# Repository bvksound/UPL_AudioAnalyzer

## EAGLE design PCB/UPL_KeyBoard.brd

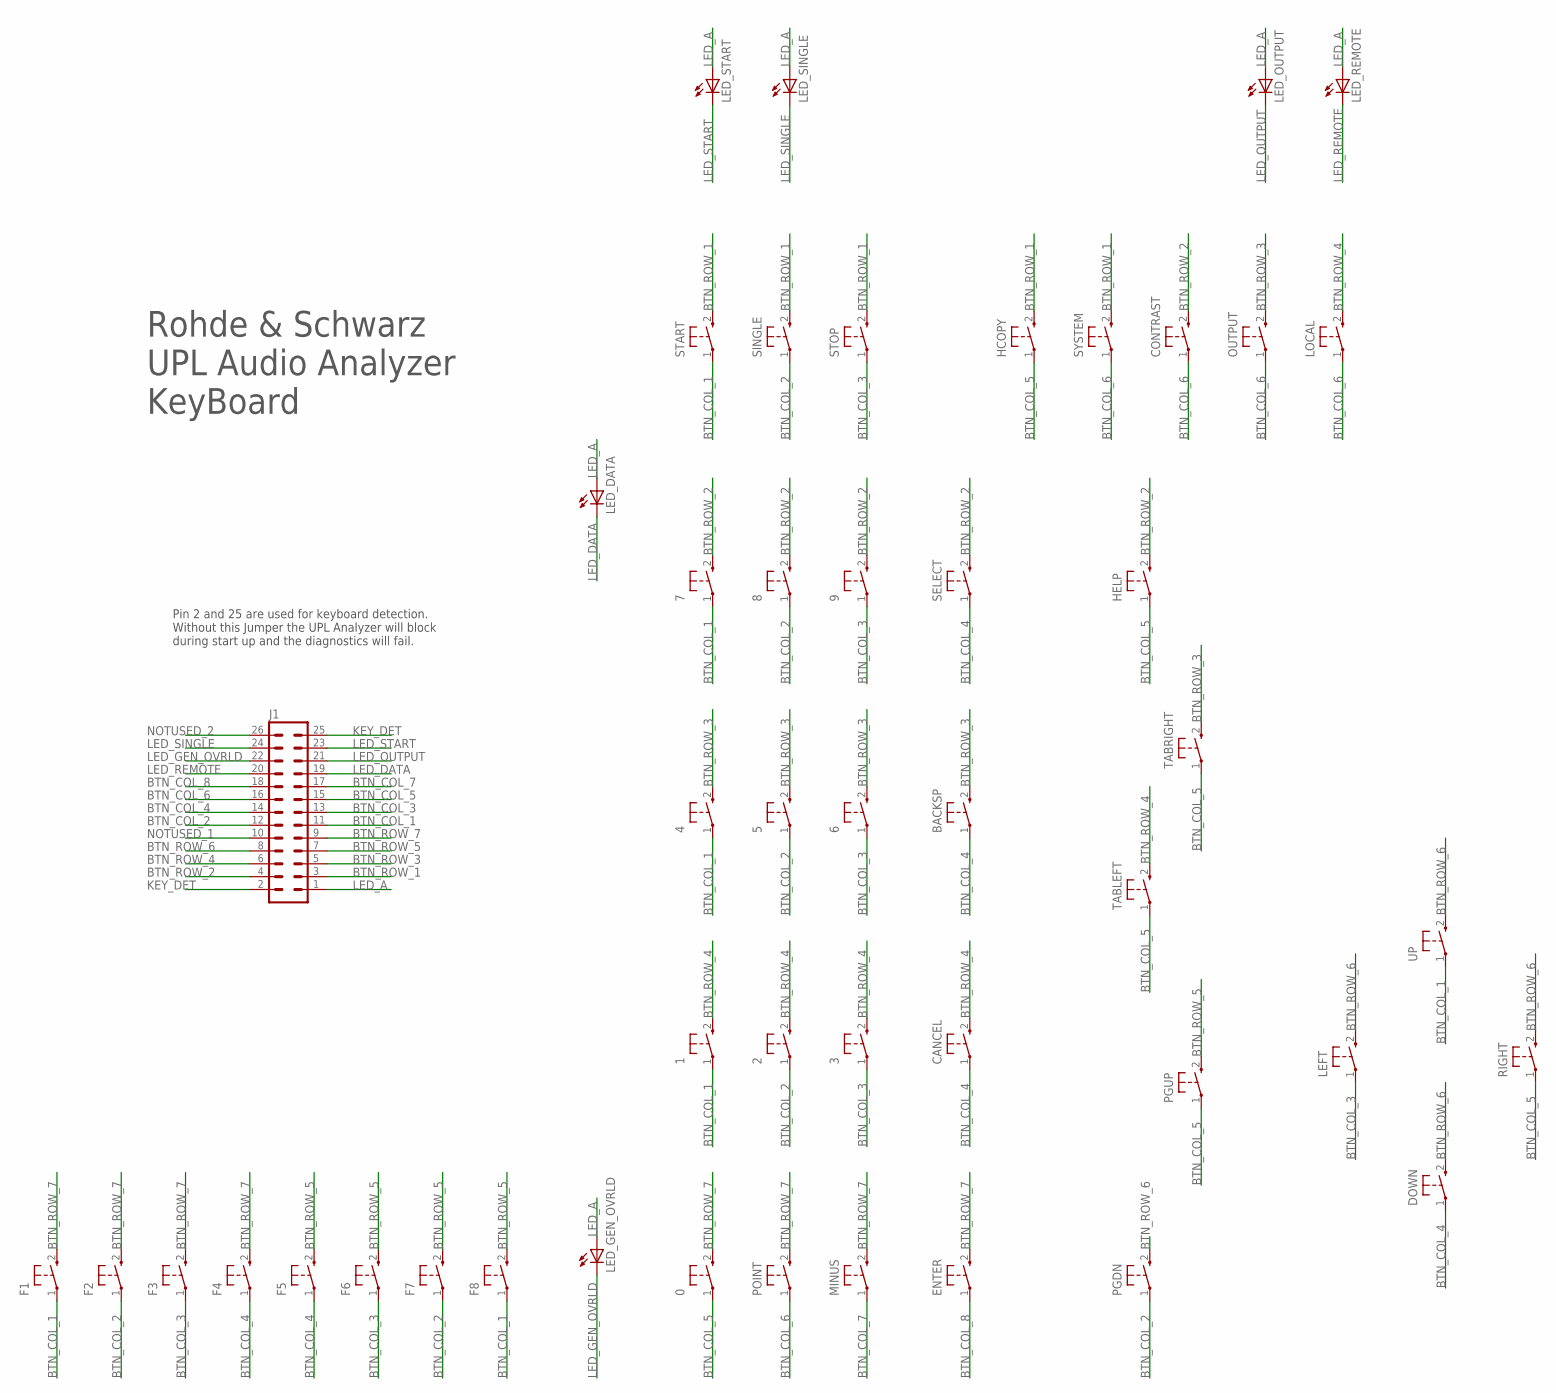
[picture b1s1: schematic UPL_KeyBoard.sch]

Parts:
0, 1, 2, 3, 4, 5, 6, 7, 8, 9: ALPS_SKQYAFE010
BACKSP: ALPS_SKQYAFE010
CANCEL: ALPS_SKQYAFE010
CONTRAST: ALPS_SKQYAFE010
DOWN: ALPS_SKQYAFE010
ENTER: ALPS_SKQYAFE010
F1, F2, F3, F4, F5, F6, F7, F8: ALPS_SKQYAFE010
HCOPY: ALPS_SKQYAFE010
HELP: ALPS_SKQYAFE010
J1: ML26
LED_DATA: LEDCHIPLED_1206; CHIPLED_1206
LED_GEN_OVRLD: LEDCHIPLED_1206; CHIPLED_1206
LED_OUTPUT: LEDCHIPLED_1206; CHIPLED_1206
LED_REMOTE: LEDCHIPLED_1206; CHIPLED_1206
LED_SINGLE: LEDCHIPLED_1206; CHIPLED_1206
LED_START: LEDCHIPLED_1206; CHIPLED_1206
LEFT: ALPS_SKQYAFE010
LOCAL: ALPS_SKQYAFE010
MINUS: ALPS_SKQYAFE010
OUTPUT: ALPS_SKQYAFE010
PGDN: ALPS_SKQYAFE010
PGUP: ALPS_SKQYAFE010
POINT: ALPS_SKQYAFE010
RIGHT: ALPS_SKQYAFE010
SELECT: ALPS_SKQYAFE010
SINGLE: ALPS_SKQYAFE010
START: ALPS_SKQYAFE010
STOP: ALPS_SKQYAFE010
SYSTEM: ALPS_SKQYAFE010
TABLEFT: ALPS_SKQYAFE010
TABRIGHT: ALPS_SKQYAFE010
UP: ALPS_SKQYAFE010

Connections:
BTN_COL_1: 1.1, 4.1, 7.1, F1.1, F8.1, J1.11, START.1, UP.1
BTN_COL_2: 2.1, 5.1, 8.1, F2.1, F7.1, J1.12, PGDN.1, SINGLE.1
BTN_COL_3: 3.1, 6.1, 9.1, F3.1, F6.1, J1.13, LEFT.1, STOP.1
BTN_COL_4: BACKSP.1, CANCEL.1, DOWN.1, F4.1, F5.1, J1.14, SELECT.1
BTN_COL_5: 0.1, HCOPY.1, HELP.1, J1.15, PGUP.1, RIGHT.1, TABLEFT.1, TABRIGHT.1
BTN_COL_6: CONTRAST.1, J1.16, LOCAL.1, OUTPUT.1, POINT.1, SYSTEM.1
BTN_COL_7: J1.17, MINUS.1
BTN_COL_8: ENTER.1, J1.18
BTN_ROW_1: HCOPY.2 (3), J1.3, SINGLE.2 (3), START.2 (3), STOP.2 (3), SYSTEM.2 (3)
BTN_ROW_2: 7.2 (3), 8.2 (3), 9.2 (3), CONTRAST.2 (3), HELP.2 (3), J1.4, SELECT.2 (3)
BTN_ROW_3: 4.2 (3), 5.2 (3), 6.2 (3), BACKSP.2 (3), J1.5, OUTPUT.2 (3), TABRIGHT.2 (3)
BTN_ROW_4: 1.2 (3), 2.2 (3), 3.2 (3), CANCEL.2 (3), J1.6, LOCAL.2 (3), TABLEFT.2 (3)
BTN_ROW_5: F5.2 (3), F6.2 (3), F7.2 (3), F8.2 (3), J1.7, PGUP.2 (3)
BTN_ROW_6: DOWN.2 (3), J1.8, LEFT.2 (3), PGDN.2 (3), RIGHT.2 (3), UP.2 (3)
BTN_ROW_7: 0.2 (3), ENTER.2 (3), F1.2 (3), F2.2 (3), F3.2 (3), F4.2 (3), J1.9, MINUS.2 (3), POINT.2 (3)
KEY_DET: J1.2, J1.25
LED_A: J1.1, LED_DATA.A, LED_GEN_OVRLD.A, LED_OUTPUT.A, LED_REMOTE.A, LED_SINGLE.A, LED_START.A
LED_DATA: J1.19, LED_DATA.C
LED_GEN_OVRLD: J1.22, LED_GEN_OVRLD.C
LED_OUTPUT: J1.21, LED_OUTPUT.C
LED_REMOTE: J1.20, LED_REMOTE.C
LED_SINGLE: J1.24, LED_SINGLE.C
LED_START: J1.23, LED_START.C
NOTUSED_1: J1.10
NOTUSED_2: J1.26

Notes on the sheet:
Pin 2 and 25 are used for keyboard detection. Without this Jumper the UPL Analyzer will block during start up and the diagnostics will fail.
Rohde & Schwarz UPL Audio Analyzer KeyBoard

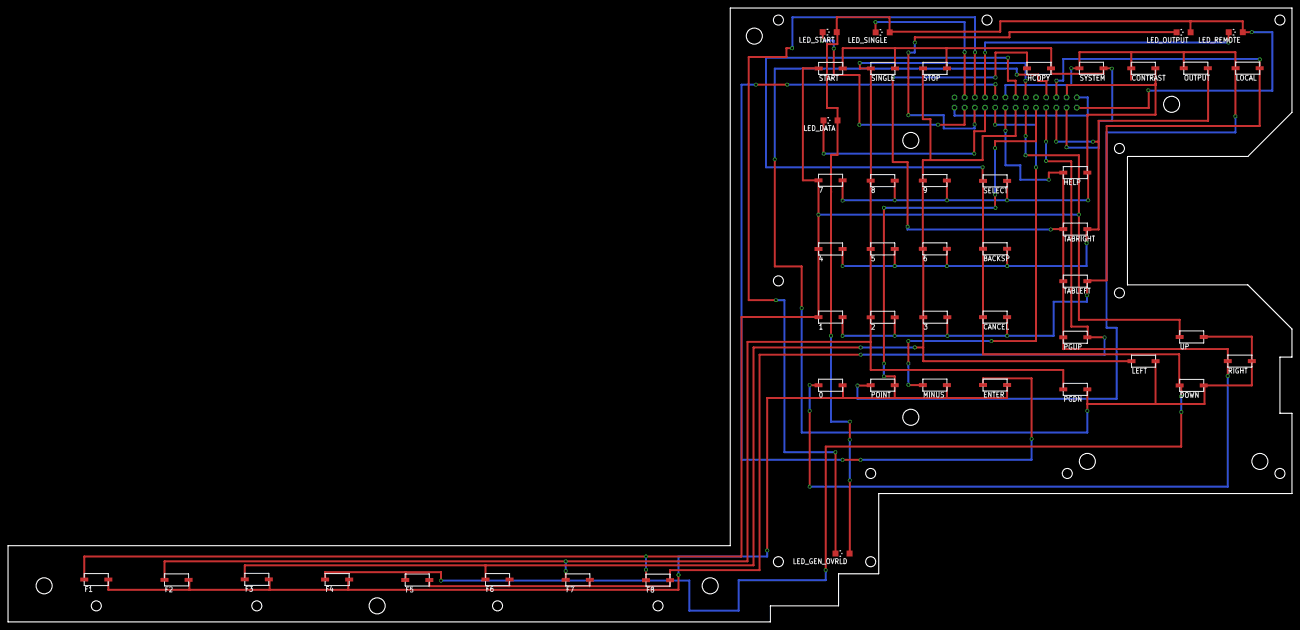
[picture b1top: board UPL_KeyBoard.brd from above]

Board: 2 copper layers, 320.0 x 153.0 mm, 48 parts (1 on the bottom side), 23 nets.

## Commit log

2020-04-14 Test Commit
2020-04-14 draft added
2020-04-19 Keyboard shortcuts added
2020-04-19 Updated design of fusion 360, also backupped in the cloud of autodesk
2020-04-19 schematic done
2020-04-20 first draft of pcb design, bom added, gerber configuration added
2020-04-20 final design added
2020-04-28 Removed trailing trace, final design, Freeze
2020-05-05 updated with remaining components
2020-05-09 basic program added
2020-11-25 add document
2021-01-23 ISA Board Added
    Reorganised + added first revision of ISA Interconnect board
2021-02-03 Membrame version draft schematic added
2021-02-13 Kicad Rev2
    Kicad design added based on new smaller ALPS buttons
2021-02-13 cleanup pcb
    cleanup move connector for more clearance screw
2021-03-18 Update of SMD button manufacturer
    Change SMD buttons to EVQQ2P02W
2021-03-20 Finalized design with FFC Connector
2021-03-26 final update rev3
2021-11-21 Rev3 updated Bom
    update outdated BOM
